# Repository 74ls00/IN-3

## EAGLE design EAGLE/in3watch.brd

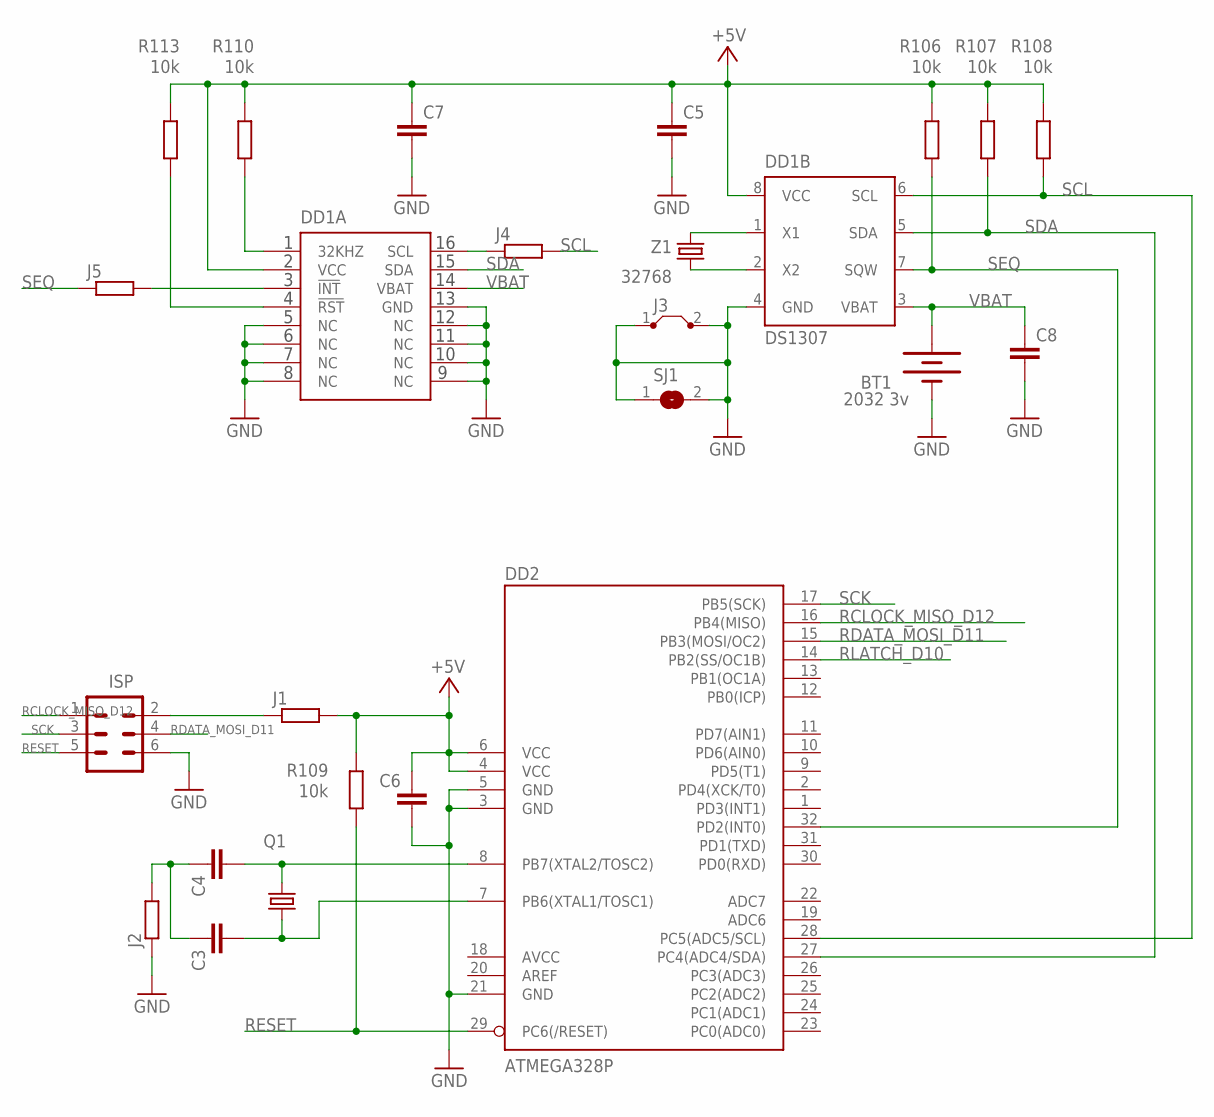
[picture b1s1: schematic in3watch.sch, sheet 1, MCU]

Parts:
BT1: 2032 3v; BATTCOM_20MM_PTH
C3, C4, C5, C6, C7: C-EUC0805; C0805
C8: C-EUC3225; C3225
DD1A: DS3231SOIC-16W; SOIC-16W
DD1B: DS1307; DIL08
DD2: ATMEGA328P; TQFP32-08
ISP: MA03-2
J1, J2: R-EU_R1206; R1206
J3: J5MM; 05
J4, J5: R-EU_R1206W; R1206W
Q1: CRYSTALHC49U70; HC49U70
R106, R107, R108, R109, R110, R113: 10k; R0805
SJ1: SJ
Z1: 32768; FC-12M

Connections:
+5V: C5.1, C6.1, C7.1, DD1A.2 (VCC), DD1B.8 (VCC), DD2.4 (VCC), DD2.6 (VCC), J1.2, R106.2, R107.2, R108.2, R109.2, R110.2, R113.2; also elsewhere on the board
+5VISP: ISP.2, J1.1
AVCC: DD2.18 (AVCC)
GND: BT1.2 (-), C5.2, C6.2, C7.2, C8.2, DD1A.5 (NC), DD1A.6 (NC), DD1A.7 (NC), DD1A.8 (NC), DD1A.9 (NC), DD1A.10 (NC), DD1A.11 (NC), DD1A.12 (NC), DD1A.13 (GND), DD1B.4 (GND), DD2.3 (GND), DD2.5 (GND), DD2.21 (GND), ISP.6, J2.1, J3.1, J3.2, SJ1.1, SJ1.2; also elsewhere on the board
unnamed: DD1B.2 (X2), Z1.P$1 (1)
unnamed: DD1B.1 (X1), Z1.P$2 (2)
unnamed: C4.2, DD2.8 (PB7(XTAL2/TOSC2)), Q1.1
unnamed: C3.1, C4.1, J2.2
unnamed: C3.2, DD2.7 (PB6(XTAL1/TOSC1)), Q1.2
unnamed: DD1A.1 (32KHZ), R110.1
unnamed: DD1A.4 (!RST), R113.1
RCLOCK_MISO_D12: DD2.16 (PB4(MISO)), ISP.1; also elsewhere on the board
RDATA_MOSI_D11: DD2.15 (PB3(MOSI/OC2)), ISP.4; also elsewhere on the board
RESET: DD2.29 (PC6(/RESET)), ISP.5, R109.1
RLATCH_D10: DD2.14 (PB2(SS/OC1B)); also elsewhere on the board
SCK: DD2.17 (PB5(SCK)), ISP.3
SCL: DD1B.6 (SCL), DD2.28 (PC5(ADC5/SCL)), J4.2, R108.1
SCL_J: DD1A.16 (SCL), J4.1
SDA: DD1A.15 (SDA), DD1B.5 (SDA), DD2.27 (PC4(ADC4/SDA)), R107.1
SEQ: DD1B.7 (SQW), DD2.32 (PD2(INT0)), J5.1, R106.1
SEQ_J: DD1A.3 (!INT), J5.2
VBAT: BT1.1 (+), C8.1, DD1A.14 (VBAT), DD1B.3 (VBAT)

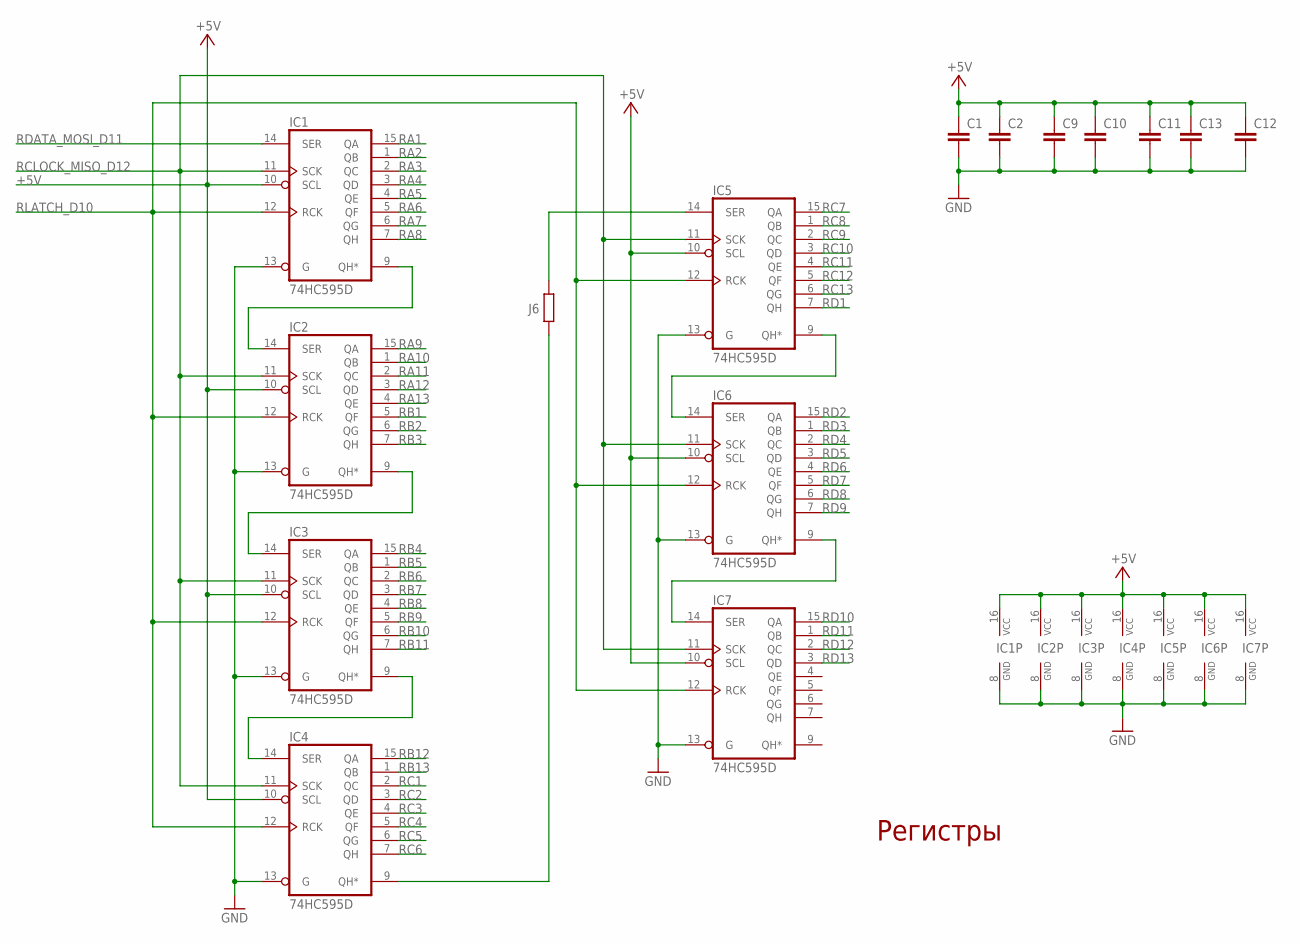
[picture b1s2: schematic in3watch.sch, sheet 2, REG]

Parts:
C1, C2, C9, C10, C11, C12, C13: C-EUC0805; C0805
IC1, IC2, IC3, IC4, IC5, IC6, IC7: 74HC595D; SO16
J6: R-EU_R1206W; R1206W

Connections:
+5V: C1.1, C2.1, C9.1, C10.1, C11.1, C12.1, C13.1, IC1.10 (SCL), IC1.16 (VCC), IC2.10 (SCL), IC2.16 (VCC), IC3.10 (SCL), IC3.16 (VCC), IC4.10 (SCL), IC4.16 (VCC), IC5.10 (SCL), IC5.16 (VCC), IC6.10 (SCL), IC6.16 (VCC), IC7.10 (SCL), IC7.16 (VCC); also elsewhere on the board
GND: C1.2, C2.2, C9.2, C10.2, C11.2, C12.2, C13.2, IC1.8 (GND), IC1.13 (G), IC2.8 (GND), IC2.13 (G), IC3.8 (GND), IC3.13 (G), IC4.8 (GND), IC4.13 (G), IC5.8 (GND), IC5.13 (G), IC6.8 (GND), IC6.13 (G), IC7.8 (GND), IC7.13 (G); also elsewhere on the board
unnamed: IC5.14 (SER), J6.2
RA1: IC1.15 (QA); also elsewhere on the board
RA2: IC1.1 (QB); also elsewhere on the board
RA3: IC1.2 (QC); also elsewhere on the board
RA4: IC1.3 (QD); also elsewhere on the board
RA5: IC1.4 (QE); also elsewhere on the board
RA6: IC1.5 (QF); also elsewhere on the board
RA7: IC1.6 (QG); also elsewhere on the board
RA8: IC1.7 (QH); also elsewhere on the board
RA9: IC2.15 (QA); also elsewhere on the board
RA10: IC2.1 (QB); also elsewhere on the board
RA11: IC2.2 (QC); also elsewhere on the board
RA12: IC2.3 (QD); also elsewhere on the board
RA13: IC2.4 (QE); also elsewhere on the board
RB1: IC2.5 (QF); also elsewhere on the board
RB2: IC2.6 (QG); also elsewhere on the board
RB3: IC2.7 (QH); also elsewhere on the board
RB4: IC3.15 (QA); also elsewhere on the board
RB5: IC3.1 (QB); also elsewhere on the board
RB6: IC3.2 (QC); also elsewhere on the board
RB7: IC3.3 (QD); also elsewhere on the board
RB8: IC3.4 (QE); also elsewhere on the board
RB9: IC3.5 (QF); also elsewhere on the board
RB10: IC3.6 (QG); also elsewhere on the board
RB11: IC3.7 (QH); also elsewhere on the board
RB12: IC4.15 (QA); also elsewhere on the board
RB13: IC4.1 (QB); also elsewhere on the board
RC1: IC4.2 (QC); also elsewhere on the board
RC2: IC4.3 (QD); also elsewhere on the board
RC3: IC4.4 (QE); also elsewhere on the board
RC4: IC4.5 (QF); also elsewhere on the board
RC5: IC4.6 (QG); also elsewhere on the board
RC6: IC4.7 (QH); also elsewhere on the board
RC7: IC5.15 (QA); also elsewhere on the board
RC8: IC5.1 (QB); also elsewhere on the board
RC9: IC5.2 (QC); also elsewhere on the board
RC10: IC5.3 (QD); also elsewhere on the board
RC11: IC5.4 (QE); also elsewhere on the board
RC12: IC5.5 (QF); also elsewhere on the board
RC13: IC5.6 (QG); also elsewhere on the board
RCLOCK_MISO_D12: IC1.11 (SCK), IC2.11 (SCK), IC3.11 (SCK), IC4.11 (SCK), IC5.11 (SCK), IC6.11 (SCK), IC7.11 (SCK); also elsewhere on the board
RD1: IC5.7 (QH); also elsewhere on the board
RD2: IC6.15 (QA); also elsewhere on the board
RD3: IC6.1 (QB); also elsewhere on the board
RD4: IC6.2 (QC); also elsewhere on the board
RD5: IC6.3 (QD); also elsewhere on the board
RD6: IC6.4 (QE); also elsewhere on the board
RD7: IC6.5 (QF); also elsewhere on the board
RD8: IC6.6 (QG); also elsewhere on the board
RD9: IC6.7 (QH); also elsewhere on the board
RD10: IC7.15 (QA); also elsewhere on the board
RD11: IC7.1 (QB); also elsewhere on the board
RD12: IC7.2 (QC); also elsewhere on the board
RD13: IC7.3 (QD); also elsewhere on the board
RDATA_MOSI_D11: IC1.14 (SER); also elsewhere on the board
RLATCH_D10: IC1.12 (RCK), IC2.12 (RCK), IC3.12 (RCK), IC4.12 (RCK), IC5.12 (RCK), IC6.12 (RCK), IC7.12 (RCK); also elsewhere on the board
SER2: IC1.9 (QH*), IC2.14 (SER)
SER3: IC2.9 (QH*), IC3.14 (SER)
SER4: IC3.9 (QH*), IC4.14 (SER)
SER5: IC4.9 (QH*), J6.1
SER6: IC5.9 (QH*), IC6.14 (SER)
SER7: IC6.9 (QH*), IC7.14 (SER)

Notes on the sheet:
Регистры

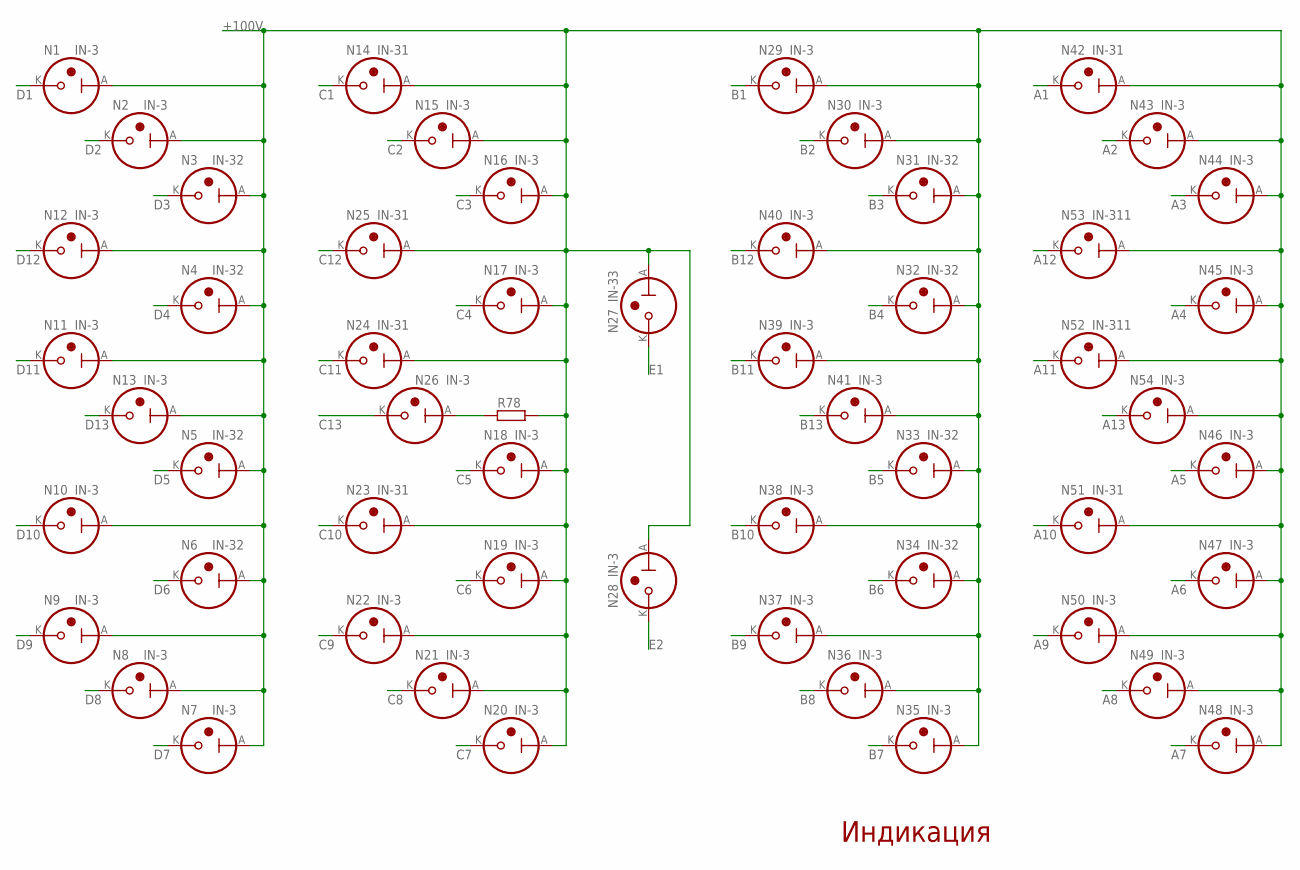
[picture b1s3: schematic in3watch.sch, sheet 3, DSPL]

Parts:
N1, N2, N7, N8, N9, N10, N11, N12, N13, N15, N16, N17, N18, N19, N20, N21, N22, N26, N28, N29, N30, N35, N36, N37, N38, N39, N40, N41, N43, N44, N45, N46, N47, N48, N49, N50, N54: IN-3
N3, N4, N5, N6, N31, N32, N33, N34: IN-32; IN-3-2
N14, N23, N24, N25, N42, N51: IN-31; IN-3-1
N27: IN-33; IN-3-3
N52, N53: IN-311; IN-3-11
R78: R-EU_0207/15; 0207/15

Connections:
+100V: N1.A, N2.A, N3.A, N4.A, N5.A, N6.A, N7.A, N8.A, N9.A, N10.A, N11.A, N12.A, N13.A, N14.A, N15.A, N16.A, N17.A, N18.A, N19.A, N20.A, N21.A, N22.A, N23.A, N24.A, N25.A, N27.A, N28.A, N29.A, N30.A, N31.A, N32.A, N33.A, N34.A, N35.A, N36.A, N37.A, N38.A, N39.A, N40.A, N41.A, N42.A, N43.A, N44.A, N45.A, N46.A, N47.A, N48.A, N49.A, N50.A, N51.A, N52.A, N53.A, N54.A, R78.2
A1: N42.K; also elsewhere on the board
A2: N43.K; also elsewhere on the board
A3: N44.K; also elsewhere on the board
A4: N45.K; also elsewhere on the board
A5: N46.K; also elsewhere on the board
A6: N47.K; also elsewhere on the board
A7: N48.K; also elsewhere on the board
A8: N49.K; also elsewhere on the board
A9: N50.K; also elsewhere on the board
A10: N51.K; also elsewhere on the board
A11: N52.K; also elsewhere on the board
A12: N53.K; also elsewhere on the board
A13: N54.K; also elsewhere on the board
B1: N29.K; also elsewhere on the board
B2: N30.K; also elsewhere on the board
B3: N31.K; also elsewhere on the board
B4: N32.K; also elsewhere on the board
B5: N33.K; also elsewhere on the board
B6: N34.K; also elsewhere on the board
B7: N35.K; also elsewhere on the board
B8: N36.K; also elsewhere on the board
B9: N37.K; also elsewhere on the board
B10: N38.K; also elsewhere on the board
B11: N39.K; also elsewhere on the board
B12: N40.K; also elsewhere on the board
B13: N41.K; also elsewhere on the board
C1: N14.K; also elsewhere on the board
C2: N15.K; also elsewhere on the board
C3: N16.K; also elsewhere on the board
C4: N17.K; also elsewhere on the board
C5: N18.K; also elsewhere on the board
C6: N19.K; also elsewhere on the board
C7: N20.K; also elsewhere on the board
C8: N21.K; also elsewhere on the board
C9: N22.K; also elsewhere on the board
C10: N23.K; also elsewhere on the board
C11: N24.K; also elsewhere on the board
C12: N25.K; also elsewhere on the board
C13: N26.K; also elsewhere on the board
D1: N1.K; also elsewhere on the board
D2: N2.K; also elsewhere on the board
D3: N3.K; also elsewhere on the board
D4: N4.K; also elsewhere on the board
D5: N5.K; also elsewhere on the board
D6: N6.K; also elsewhere on the board
D7: N7.K; also elsewhere on the board
D8: N8.K; also elsewhere on the board
D9: N9.K; also elsewhere on the board
D10: N10.K; also elsewhere on the board
D11: N11.K; also elsewhere on the board
D12: N12.K; also elsewhere on the board
D13: N13.K; also elsewhere on the board
E1: N27.K; also elsewhere on the board
E2: N28.K; also elsewhere on the board
unnamed: N26.A, R78.1

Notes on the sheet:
Индикация

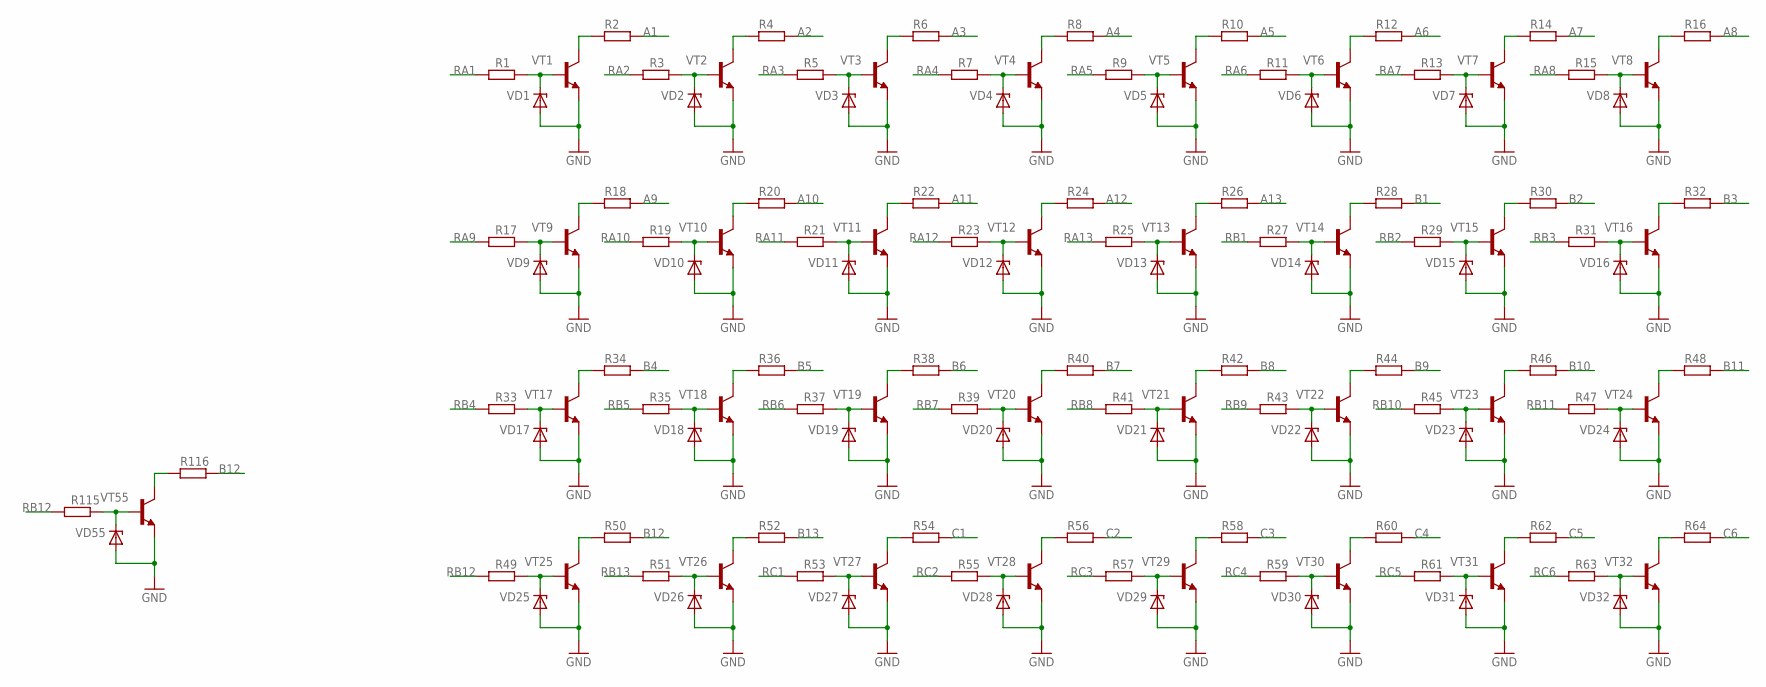
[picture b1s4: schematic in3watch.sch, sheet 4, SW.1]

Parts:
R1, R3, R5, R7, R9, R11, R13, R15, R17, R21, R23, R25, R27, R29, R31, R33, R37, R39, R47, R49, R51, R53, R55, R57, R59, R61, R63: R-EU_R0805; R0805
R2, R4, R6, R8, R10, R12, R14, R16, R18, R20, R22, R24, R26, R28, R30, R32, R34, R36, R38, R40, R42, R44, R46, R50, R52, R54, R58, R60, R62, R64: R-EU_0207/12; 0207/12
R19, R41, R43, R45: R-EU_R1206W; R1206W
R35: R-EU_M1206; M1206
R48, R56: R-EU_0207/10; 0207/10
R115, R116: R-EU_R0603; R0603
VD1, VD2, VD3, VD4, VD5, VD6, VD7, VD8, VD9, VD10, VD11, VD12, VD13, VD14, VD15, VD16, VD17, VD18, VD19, VD20, VD21, VD22, VD23, VD24, VD25, VD26, VD27, VD28, VD29, VD30, VD31, VD32, VD55: ZENER-DIODESOD80C; SOD80C
VT1, VT2, VT3, VT4, VT5, VT6, VT7, VT8, VT9, VT10, VT11, VT12, VT13, VT14, VT15, VT16, VT17, VT18, VT19, VT20, VT21, VT22, VT23, VT24, VT25, VT26, VT27, VT28, VT29, VT30, VT31, VT32, VT55: BC849SMD; SOT23-BEC

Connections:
A1: R2.2; also elsewhere on the board
A2: R4.2; also elsewhere on the board
A3: R6.2; also elsewhere on the board
A4: R8.2; also elsewhere on the board
A5: R10.2; also elsewhere on the board
A6: R12.2; also elsewhere on the board
A7: R14.2; also elsewhere on the board
A8: R16.2; also elsewhere on the board
A9: R18.2; also elsewhere on the board
A10: R20.2; also elsewhere on the board
A11: R22.2; also elsewhere on the board
A12: R24.2; also elsewhere on the board
A13: R26.2; also elsewhere on the board
B1: R28.2; also elsewhere on the board
B2: R30.2; also elsewhere on the board
B3: R32.2; also elsewhere on the board
B4: R34.2; also elsewhere on the board
B5: R36.2; also elsewhere on the board
B6: R38.2; also elsewhere on the board
B7: R40.2; also elsewhere on the board
B8: R42.2; also elsewhere on the board
B9: R44.2; also elsewhere on the board
B10: R46.2; also elsewhere on the board
B11: R48.2; also elsewhere on the board
B12: R50.2, R116.2; also elsewhere on the board
B13: R52.2; also elsewhere on the board
C1: R54.2; also elsewhere on the board
C2: R56.2; also elsewhere on the board
C3: R58.2; also elsewhere on the board
C4: R60.2; also elsewhere on the board
C5: R62.2; also elsewhere on the board
C6: R64.2; also elsewhere on the board
GND: VD1.A, VD2.A, VD3.A, VD4.A, VD5.A, VD6.A, VD7.A, VD8.A, VD9.A, VD10.A, VD11.A, VD12.A, VD13.A, VD14.A, VD15.A, VD16.A, VD17.A, VD18.A, VD19.A, VD20.A, VD21.A, VD22.A, VD23.A, VD24.A, VD25.A, VD26.A, VD27.A, VD28.A, VD29.A, VD30.A, VD31.A, VD32.A, VD55.A, VT1.E, VT2.E, VT3.E, VT4.E, VT5.E, VT6.E, VT7.E, VT8.E, VT9.E, VT10.E, VT11.E, VT12.E, VT13.E, VT14.E, VT15.E, VT16.E, VT17.E, VT18.E, VT19.E, VT20.E, VT21.E, VT22.E, VT23.E, VT24.E, VT25.E, VT26.E, VT27.E, VT28.E, VT29.E, VT30.E, VT31.E, VT32.E, VT55.E; also elsewhere on the board
unnamed: R2.1, VT1.C
unnamed: R1.2, VD1.C, VT1.B
unnamed: R34.1, VT17.C
unnamed: R4.1, VT2.C
unnamed: R3.2, VD2.C, VT2.B
unnamed: R18.1, VT9.C
unnamed: R17.2, VD9.C, VT9.B
unnamed: R20.1, VT10.C
unnamed: R19.2, VD10.C, VT10.B
unnamed: R22.1, VT11.C
unnamed: R21.2, VD11.C, VT11.B
unnamed: R24.1, VT12.C
unnamed: R23.2, VD12.C, VT12.B
unnamed: R26.1, VT13.C
unnamed: R25.2, VD13.C, VT13.B
unnamed: R28.1, VT14.C
unnamed: R6.1, VT3.C
unnamed: R5.2, VD3.C, VT3.B
unnamed: R8.1, VT4.C
unnamed: R7.2, VD4.C, VT4.B
unnamed: R10.1, VT5.C
unnamed: R9.2, VD5.C, VT5.B
unnamed: R12.1, VT6.C
unnamed: R11.2, VD6.C, VT6.B
unnamed: R14.1, VT7.C
unnamed: R13.2, VD7.C, VT7.B
unnamed: R16.1, VT8.C
unnamed: R15.2, VD8.C, VT8.B
unnamed: R27.2, VD14.C, VT14.B
unnamed: R33.2, VD17.C, VT17.B
unnamed: R30.1, VT15.C
unnamed: R29.2, VD15.C, VT15.B
unnamed: R32.1, VT16.C
unnamed: R31.2, VD16.C, VT16.B
unnamed: R36.1, VT18.C
unnamed: R35.2, VD18.C, VT18.B
unnamed: R38.1, VT19.C
unnamed: R37.2, VD19.C, VT19.B
unnamed: R40.1, VT20.C
unnamed: R39.2, VD20.C, VT20.B
unnamed: R42.1, VT21.C
unnamed: R41.2, VD21.C, VT21.B
unnamed: R44.1, VT22.C
unnamed: R43.2, VD22.C, VT22.B
unnamed: R46.1, VT23.C
unnamed: R45.2, VD23.C, VT23.B
unnamed: R48.1, VT24.C
unnamed: R47.2, VD24.C, VT24.B
unnamed: R50.1, VT25.C
unnamed: R49.2, VD25.C, VT25.B
unnamed: R52.1, VT26.C
unnamed: R51.2, VD26.C, VT26.B
unnamed: R54.1, VT27.C
unnamed: R53.2, VD27.C, VT27.B
unnamed: R56.1, VT28.C
unnamed: R55.2, VD28.C, VT28.B
unnamed: R58.1, VT29.C
unnamed: R57.2, VD29.C, VT29.B
unnamed: R60.1, VT30.C
unnamed: R59.2, VD30.C, VT30.B
unnamed: R62.1, VT31.C
unnamed: R61.2, VD31.C, VT31.B
unnamed: R64.1, VT32.C
unnamed: R63.2, VD32.C, VT32.B
unnamed: R116.1, VT55.C
unnamed: R115.2, VD55.C, VT55.B
RA1: R1.1; also elsewhere on the board
RA2: R3.1; also elsewhere on the board
RA3: R5.1; also elsewhere on the board
RA4: R7.1; also elsewhere on the board
RA5: R9.1; also elsewhere on the board
RA6: R11.1; also elsewhere on the board
RA7: R13.1; also elsewhere on the board
RA8: R15.1; also elsewhere on the board
RA9: R17.1; also elsewhere on the board
RA10: R19.1; also elsewhere on the board
RA11: R21.1; also elsewhere on the board
RA12: R23.1; also elsewhere on the board
RA13: R25.1; also elsewhere on the board
RB1: R27.1; also elsewhere on the board
RB2: R29.1; also elsewhere on the board
RB3: R31.1; also elsewhere on the board
RB4: R33.1; also elsewhere on the board
RB5: R35.1; also elsewhere on the board
RB6: R37.1; also elsewhere on the board
RB7: R39.1; also elsewhere on the board
RB8: R41.1; also elsewhere on the board
RB9: R43.1; also elsewhere on the board
RB10: R45.1; also elsewhere on the board
RB11: R47.1; also elsewhere on the board
RB12: R49.1, R115.1; also elsewhere on the board
RB13: R51.1; also elsewhere on the board
RC1: R53.1; also elsewhere on the board
RC2: R55.1; also elsewhere on the board
RC3: R57.1; also elsewhere on the board
RC4: R59.1; also elsewhere on the board
RC5: R61.1; also elsewhere on the board
RC6: R63.1; also elsewhere on the board

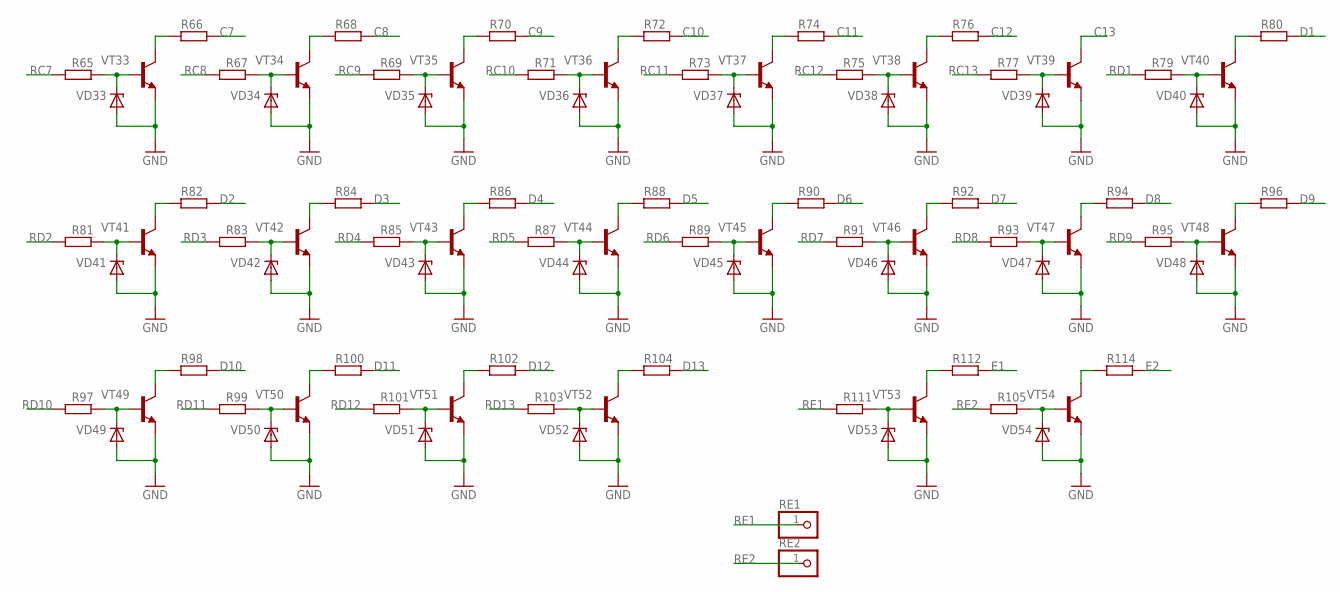
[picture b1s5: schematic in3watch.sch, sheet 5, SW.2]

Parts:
R65, R67, R69, R71, R73, R77, R79, R81, R83, R85, R87, R89, R93, R95, R97, R99, R101, R103, R105, R111: R-EU_R0805; R0805
R66, R68, R70, R72, R74, R80, R82, R84, R86, R88, R90, R91, R92, R94, R96, R98, R100, R102: R-EU_0207/12; 0207/12
R75: R-EU_R1206W; R1206W
R76: R-EU_0207/10; 0207/10
R104: R-EU_0207/15; 0207/15
R112, R114: R-EU_M0805; M0805
RE1, RE2: PINHD-1X1; 1X01
VD33, VD34, VD35, VD36, VD37, VD38, VD39, VD40, VD41, VD42, VD43, VD44, VD45, VD46, VD47, VD48, VD49, VD50, VD51, VD52, VD53, VD54: ZENER-DIODESOD80C; SOD80C
VT33, VT34, VT35, VT36, VT37, VT38, VT39, VT40, VT41, VT42, VT43, VT44, VT45, VT46, VT47, VT48, VT49, VT50, VT51, VT52, VT53, VT54: BC849SMD; SOT23-BEC

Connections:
C7: R66.2; also elsewhere on the board
C8: R68.2; also elsewhere on the board
C9: R70.2; also elsewhere on the board
C10: R72.2; also elsewhere on the board
C11: R74.2; also elsewhere on the board
C12: R76.2; also elsewhere on the board
C13: VT39.C; also elsewhere on the board
D1: R80.2; also elsewhere on the board
D2: R82.2; also elsewhere on the board
D3: R84.2; also elsewhere on the board
D4: R86.2; also elsewhere on the board
D5: R88.2; also elsewhere on the board
D6: R90.2; also elsewhere on the board
D7: R92.2; also elsewhere on the board
D8: R94.2; also elsewhere on the board
D9: R96.2; also elsewhere on the board
D10: R98.2; also elsewhere on the board
D11: R100.2; also elsewhere on the board
D12: R102.2; also elsewhere on the board
D13: R104.2; also elsewhere on the board
E1: R112.2; also elsewhere on the board
E2: R114.2; also elsewhere on the board
GND: VD33.A, VD34.A, VD35.A, VD36.A, VD37.A, VD38.A, VD39.A, VD40.A, VD41.A, VD42.A, VD43.A, VD44.A, VD45.A, VD46.A, VD47.A, VD48.A, VD49.A, VD50.A, VD51.A, VD52.A, VD53.A, VD54.A, VT33.E, VT34.E, VT35.E, VT36.E, VT37.E, VT38.E, VT39.E, VT40.E, VT41.E, VT42.E, VT43.E, VT44.E, VT45.E, VT46.E, VT47.E, VT48.E, VT49.E, VT50.E, VT51.E, VT52.E, VT53.E, VT54.E; also elsewhere on the board
unnamed: R66.1, VT33.C
unnamed: R65.2, VD33.C, VT33.B
unnamed: R68.1, VT34.C
unnamed: R67.2, VD34.C, VT34.B
unnamed: R112.1, VT53.C
unnamed: R70.1, VT35.C
unnamed: R69.2, VD35.C, VT35.B
unnamed: R72.1, VT36.C
unnamed: R71.2, VD36.C, VT36.B
unnamed: R74.1, VT37.C
unnamed: R73.2, VD37.C, VT37.B
unnamed: R76.1, VT38.C
unnamed: R75.2, VD38.C, VT38.B
unnamed: R111.2, VD53.C, VT53.B
unnamed: R77.2, VD39.C, VT39.B
unnamed: R80.1, VT40.C
unnamed: R79.2, VD40.C, VT40.B
unnamed: R82.1, VT41.C
unnamed: R81.2, VD41.C, VT41.B
unnamed: R84.1, VT42.C
unnamed: R83.2, VD42.C, VT42.B
unnamed: R86.1, VT43.C
unnamed: R85.2, VD43.C, VT43.B
unnamed: R88.1, VT44.C
unnamed: R87.2, VD44.C, VT44.B
unnamed: R90.1, VT45.C
unnamed: R89.2, VD45.C, VT45.B
unnamed: R92.1, VT46.C
unnamed: R91.2, VD46.C, VT46.B
unnamed: R94.1, VT47.C
unnamed: R93.2, VD47.C, VT47.B
unnamed: R96.1, VT48.C
unnamed: R95.2, VD48.C, VT48.B
unnamed: R98.1, VT49.C
unnamed: R97.2, VD49.C, VT49.B
unnamed: R100.1, VT50.C
unnamed: R99.2, VD50.C, VT50.B
unnamed: R102.1, VT51.C
unnamed: R101.2, VD51.C, VT51.B
unnamed: R104.1, VT52.C
unnamed: R103.2, VD52.C, VT52.B
unnamed: R114.1, VT54.C
unnamed: R105.2, VD54.C, VT54.B
RC7: R65.1; also elsewhere on the board
RC8: R67.1; also elsewhere on the board
RC9: R69.1; also elsewhere on the board
RC10: R71.1; also elsewhere on the board
RC11: R73.1; also elsewhere on the board
RC12: R75.1; also elsewhere on the board
RC13: R77.1; also elsewhere on the board
RD1: R79.1; also elsewhere on the board
RD2: R81.1; also elsewhere on the board
RD3: R83.1; also elsewhere on the board
RD4: R85.1; also elsewhere on the board
RD5: R87.1; also elsewhere on the board
RD6: R89.1; also elsewhere on the board
RD7: R91.1; also elsewhere on the board
RD8: R93.1; also elsewhere on the board
RD9: R95.1; also elsewhere on the board
RD10: R97.1; also elsewhere on the board
RD11: R99.1; also elsewhere on the board
RD12: R101.1; also elsewhere on the board
RD13: R103.1; also elsewhere on the board
RE1: R111.1, RE1.1
RE2: R105.1, RE2.1

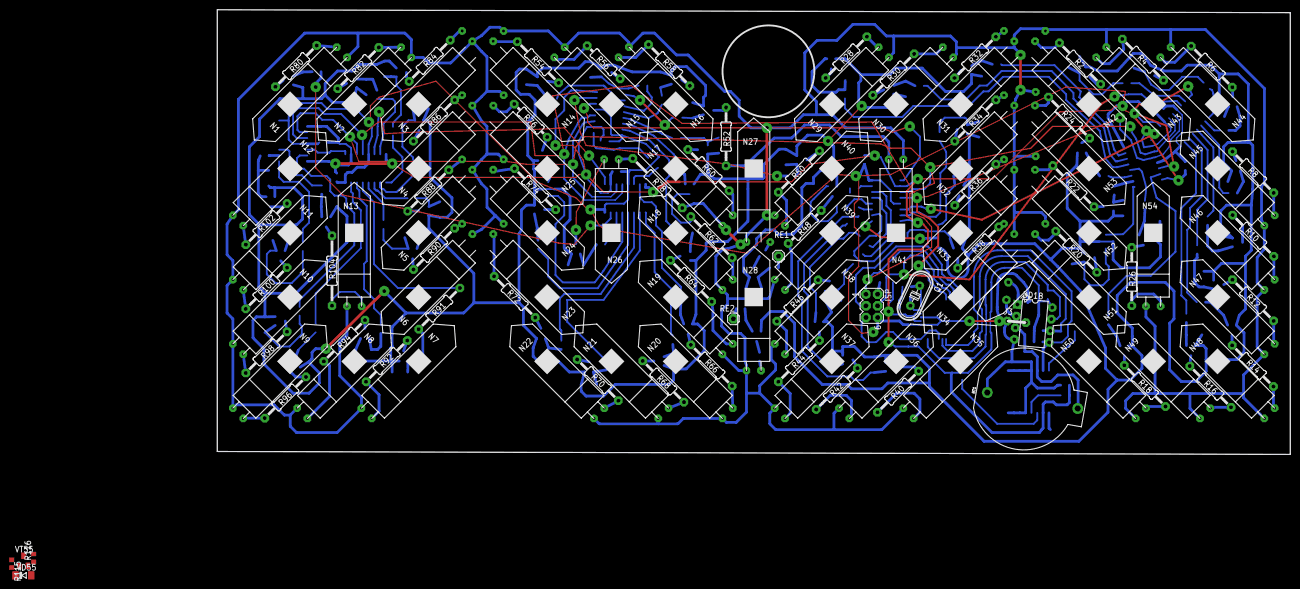
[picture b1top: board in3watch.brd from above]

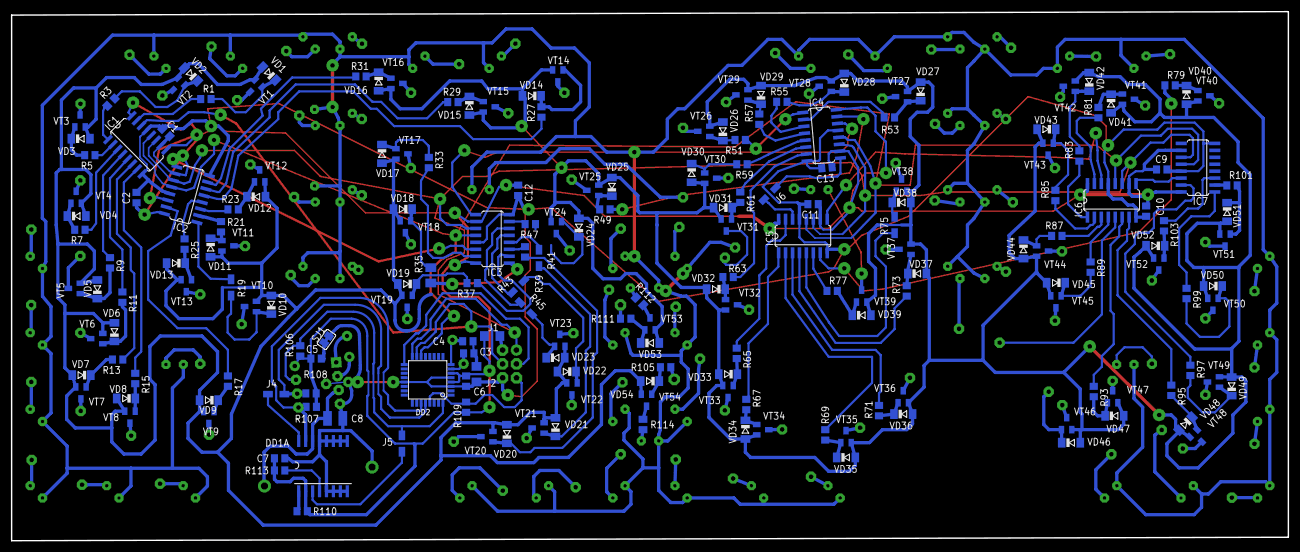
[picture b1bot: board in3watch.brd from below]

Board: 2 copper layers, 233.7 x 96.8 mm, 316 parts (197 on the bottom side), 247 nets.

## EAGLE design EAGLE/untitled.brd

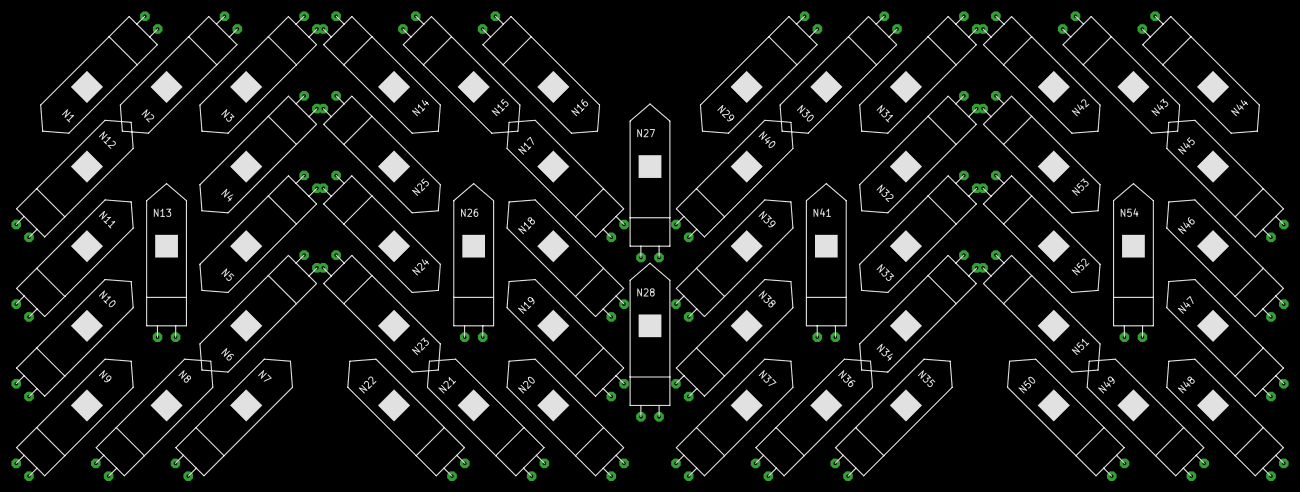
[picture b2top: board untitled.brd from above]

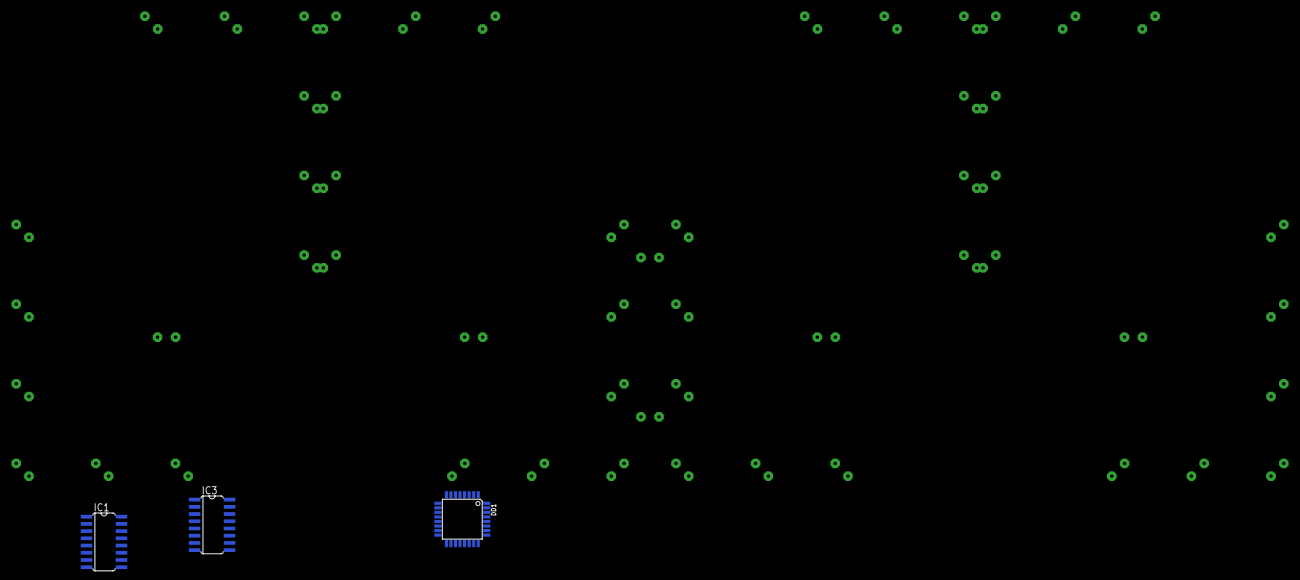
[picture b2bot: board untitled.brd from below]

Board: 2 copper layers, 57 parts (3 on the bottom side), 2 nets, no tracks yet.

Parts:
DD1: MEGA8-AI; TQFP32-08
IC1, IC3: 74HC595D; SO16
N1, N2, N3, N4, N5, N6, N7, N8, N9, N10, N11, N12, N13, N14, N15, N16, N17, N18, N19, N20, N21, N22, N23, N24, N25, N26, N27, N28, N29, N30, N31, N32, N33, N34, N35, N36, N37, N38, N39, N40, N41, N42, N43, N44, N45, N46, N47, N48, N49, N50, N51, N52, N53, N54: IN-3

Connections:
GND: DD1.3, DD1.5, DD1.21, IC1.8, IC3.8
VCC: DD1.4, DD1.6, IC1.16, IC3.16

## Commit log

2019-01-21 all 4d
2019-01-22 победа
2019-01-22 экран готов
2019-01-24 победа 0
2019-01-24 победа 0 v2
2019-01-25 ind vs st
2019-10-18 e1e2
2019-10-21 +dot2
2021-04-26 qimg

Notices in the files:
parts and their libraries:
SparkFun-Batteries: Licensing: Creative Commons ShareAlike 4.0 International - https://creativecommons.org/licenses/by-sa/4.0
